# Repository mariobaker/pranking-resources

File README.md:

# Pranking Resources
recipes for successful pranking

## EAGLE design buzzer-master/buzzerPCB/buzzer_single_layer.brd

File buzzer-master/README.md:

# Buzzer
Small buzzer to hide and will go off randomly, designed to be simple, cheap, and compact. Intended to be disposable.
The code can run on any Arduino or microcontroller, all you need is one digital output pin!

_Notes: The buzzer is meant to annoy for as long as possible without getting removed. To that end, try to ensure you don't ring too often or for too long otherwise it will give people more of a reason to be search for it, and make it easier to locate._

**_This system can be adapted to other things you want to go off randomly that can be controlled 'digitally', like lights or solenoids._**

### Approaches
There are to ways to approach this prank, the easiest is using an Arduino or another similar development board. This will reduce the complexity and labour needed, but potentially increase cost.

The other approach is making an embedded system. This will require more logistics to set up but will pay off when scaled up. This is based around programming a microcontroller directly; the provided designs use an ATtiny85 (should work for with a ATtiny13/25/45 as well) and making a circuit board or using a protoboard to connect other components.

### Easy route (Using an Arduino)
So you've decided to take the easier route, no shame in that.

#### Bill of materials
All these parts can be readily found in most hobbyist stores, such as Creatron. The tools can be borrowed from B&G.
- Arduino or other dev board. The Arduino Nano is particularly well suited for this
- Power source, ideally batteries. Should be >=6V, 9V batteries are simpler and cheaper than 4 AAs but won't last as long.
  - Connector for power source if needed. Having pre-installed lead wires makes things easier.
- DC buzzer
- Wire

Tools:
- Soldering iron
- Solder wire
- Electrical tape (optional)

#### Assembly
1. Solder your power source ground (negative, usually black) to any ground (GND) on the dev board
   - Skip this and the next step if you are using a power supply you can just plug into your dev board
2. Solder your power source positive (usually red) to the input power (VIN) or equivalent on the dev board
3. Solder the positive end of the buzzer to a digital output on you board
   - **Avoid pins D0 and D1 on Arduinos! Use D2 instead.**
4. Solder the negative end of the buzzer to a ground (GND) pin on the dev board

#### Programming and Deployment
1. Connect your dev board to your computer
2. Download and open the sketch in the "buzz" folder in your IDE of choice (probably Arduino)
3. Apply an adjustment you would like to the code
   - **Make sure you set the buzzer pin to the right value**
4. Upload the code to the dev board and see if it works
5. Before deploying, disconnect the board from the computer and use your final power source until you are certain it will work.
   - Observing two or three bursts should suffice.
   - If you are impatient you can upload a version with shorter intervals to have it run through a couple bursts quickly before reverting to your old values

### Harder Route (Embedded Design)
This will require more prep than the other route but can pay off if you are going for scale or merely the learning experience. The instructions for this will be more open ended than the other, as it is assumed you know or are more willing to figure things out.

### Bill of materials
- Microcontroller (ATtiny85 was used in the provided design)
  - Look into getting an IC socket so you can easily remove the microcontroller to reprogram it, at least for your first unit.
- DC buzzer
- 5V regulator (100mA capacity is plenty) (78L05Z is used in the design)
- NPN transistor or N-channel MOSFET (2N3904 was used)
- Two 1kOhm resistors
- 100nF capacitor (>=6V rating)
- Circuit boards or protoboard

Tools:
- You ought to know
- Breadboard (if using Arduino as ISP, see [Programming](#programming))
- Jumper wires (if using Arduino as ISP, see [Programming](#programming))
- Arduino (if using Arduino as ISP, see [Programming](#programming))

### Preparing circuit boards (if desired)
If you decide to have circuit boards made, there are EAGLE files prepared for you in the "buzzerPCB" folder. There are two versions, one that is more compact and makes use of surface mount parts which should be sent off to a professional PCB manufacturer to be made if desired. Due its size and shape it is easily panelized so you can easily get dozens of these made.

The other version is a single layer variant which uses entirely through-hole components. This one is meant to be made using the MIE makerspace (**_they'll make them free of charge_**, just don't be a dick to them) or anywhere else circuit boards can get milled. 

If you want to reach out to the MIE makerspace look them up on the MIE website, ask Mario, or ask third or fourth year mechs for help. We will not post their contact info here.

### Assembly
You've probably got this figured out anyway. Straight forward circuit board assembly if you went that way, if you opted for protoboard, good luck. Hopefully you can find some help in the schematics if needed regardless of the path chosen.

### Programming
Programming embedded microcontroller is up to you. A tried and true method we've used for AVR microcontrollers is using an Arduino as an ISP option in the Arduino IDE, this is pretty cheap since any spare Arduino can really used and it only requires six (6) jumpers and a breadboard to seat the microcontroller being programmed. However the details are out of the scope of a README like this so here's a link to a good tutorial for [programming an ATtiny85 using an Arduino as an ISP](https://create.arduino.cc/projecthub/arjun/programming-attiny85-with-arduino-uno-afb829). It will cover everything you need assuming you already have some core knowledge in using Arduinos.

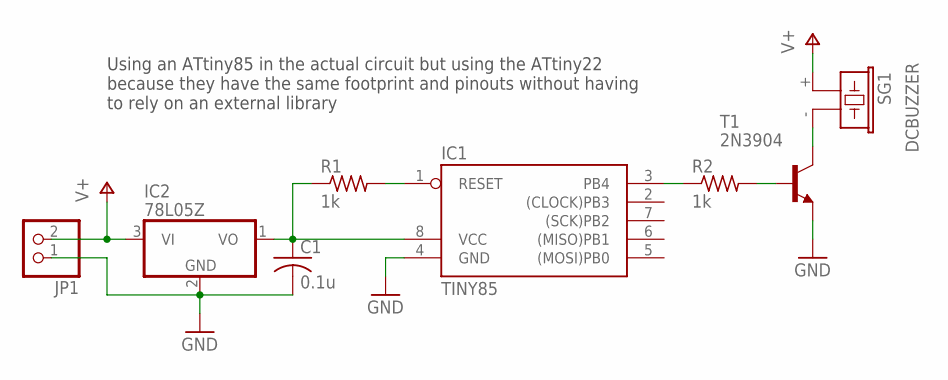
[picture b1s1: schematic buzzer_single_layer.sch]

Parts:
C1: 0.1u; C025-050X050
IC1: TINY85; DIL08
IC2: 78L05Z; TO92
JP1: PINHD-1X2; 1X02
R1, R2: 1k; 0204/7
SG1: DCBUZZER; F/CM12P
T1: 2N3904; TO92

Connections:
5V: C1.1, IC1.8 (VCC), IC2.1 (VO), R1.1
BUZ_NEG: SG1.- (2), T1.1 (C)
GND: C1.2, IC1.4 (GND), IC2.2 (GND), JP1.1, T1.3 (E)
unnamed: R2.2, T1.2 (B)
unnamed: IC1.3 (PB4), R2.1
RESET: IC1.1 (RESET), R1.2
V+: IC2.3 (VI), JP1.2, SG1.+ (1)

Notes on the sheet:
Using an ATtiny85 in the actual circuit but using the ATtiny22 because they have the same footprint and pinouts without having to rely on an external library

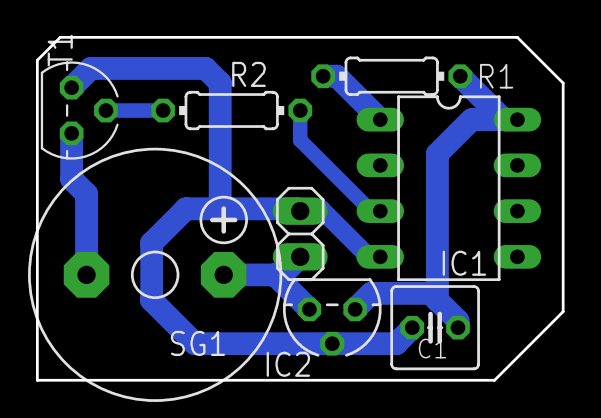
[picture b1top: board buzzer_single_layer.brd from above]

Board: 2 copper layers, 29.2 x 19.1 mm, 8 parts (0 on the bottom side), 7 nets.

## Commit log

2020-06-20 Add README.md
